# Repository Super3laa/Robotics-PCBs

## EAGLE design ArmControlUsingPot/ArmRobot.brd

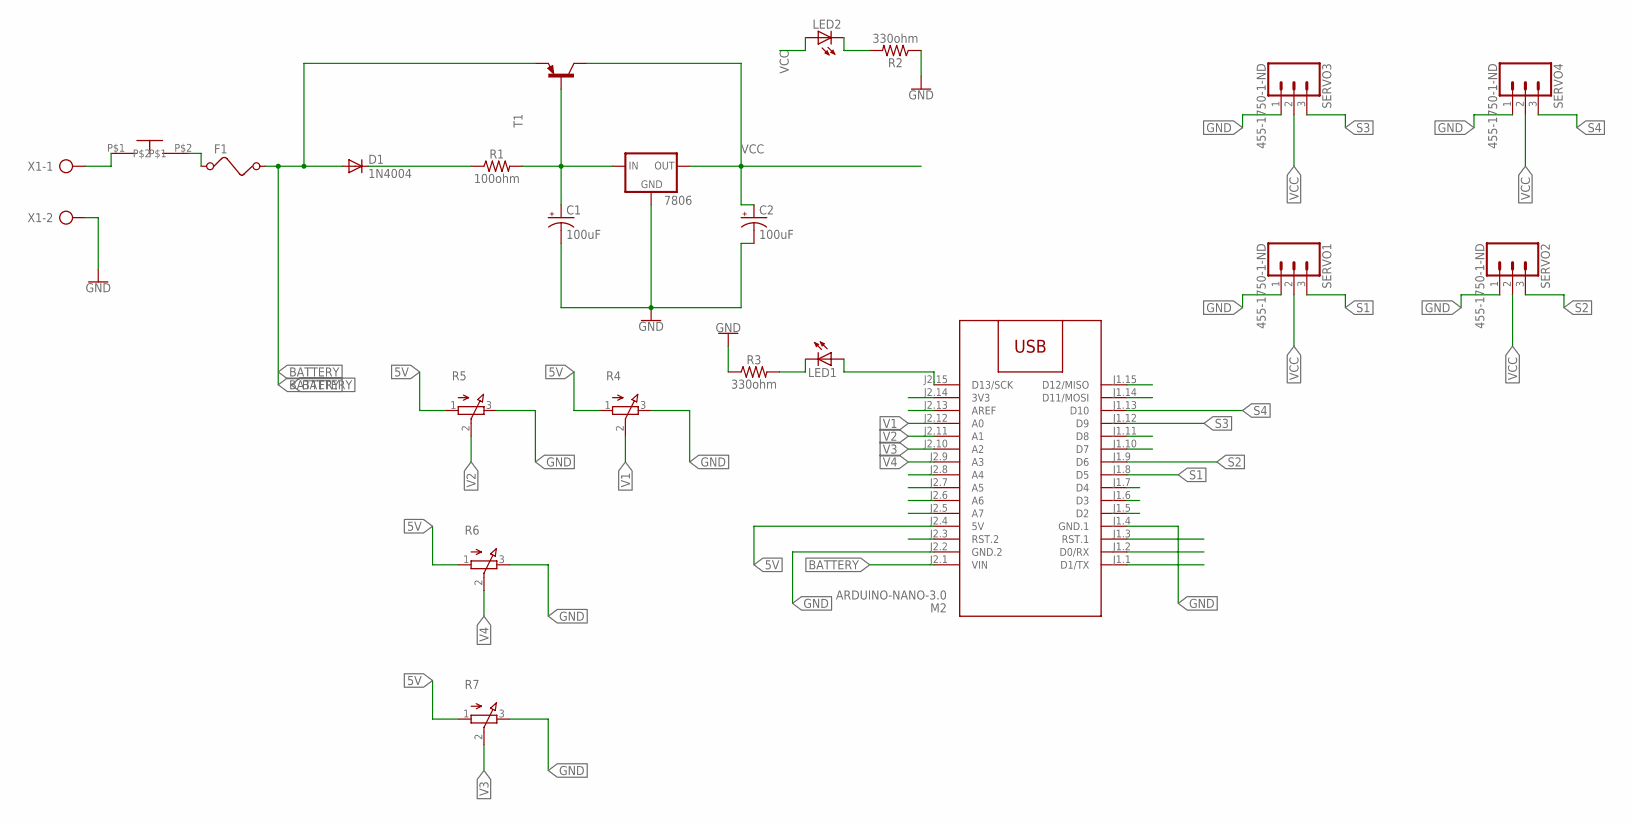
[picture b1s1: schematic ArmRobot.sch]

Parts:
7806: 78XXS
C1, C2: 100uF; CPOL-RADIAL-2.5MM-6.5MM
D1: 1N4004; DO41-10
F1: FUSE
LED1, LED2: LED3MM
M2: ARDUINO-NANO-3.0
R1: 100ohm; AXIAL-0.3
R2, R3: 330ohm; AXIAL-0.3
R4, R5, R6, R7: 3RP/1610N
SERVO1, SERVO2, SERVO3, SERVO4: 455-1750-1-ND; 1X03
T1: -PNP-TO220V; TO220V
U$1: ON_OFF
X1: AK500/2-H

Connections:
5V: M2.J2.4 (5V), R4.1 (A), R5.1 (A), R6.1 (A), R7.1 (A)
BATTERY: D1.A, F1.2, M2.J2.1 (VIN), T1.3 (E)
BATTERY_INPUT: U$1.P$1, X1.1
GND: 7806.GND, C1.2 (-), C2.2 (-), M2.J1.4 (GND.1), M2.J2.2 (GND.2), R2.P$1 (1), R3.P$1 (1), R4.3 (E), R5.3 (E), R6.3 (E), R7.3 (E), SERVO1.1, SERVO2.1, SERVO3.1, SERVO4.1, X1.2
unnamed: LED1.K (C), R3.P$2 (2)
unnamed: LED1.A, M2.J2.15 (D13/SCK)
unnamed: D1.C, R1.P$1 (1)
unnamed: 7806.IN, C1.1 (+), R1.P$2 (2), T1.1 (B)
unnamed: F1.1, U$1.P$2
unnamed: LED2.K (C), R2.P$2 (2)
S1: M2.J1.8 (D5), SERVO1.3
S2: M2.J1.9 (D6), SERVO2.3
S3: M2.J1.12 (D9), SERVO3.3
S4: M2.J1.13 (D10), SERVO4.3
V1: M2.J2.12 (A0), R4.2 (S)
V2: M2.J2.11 (A1), R5.2 (S)
V3: M2.J2.10 (A2), R7.2 (S)
V4: M2.J2.9 (A3), R6.2 (S)
VCC: 7806.OUT, C2.1 (+), LED2.A, SERVO1.2, SERVO2.2, SERVO3.2, SERVO4.2, T1.2 (C)

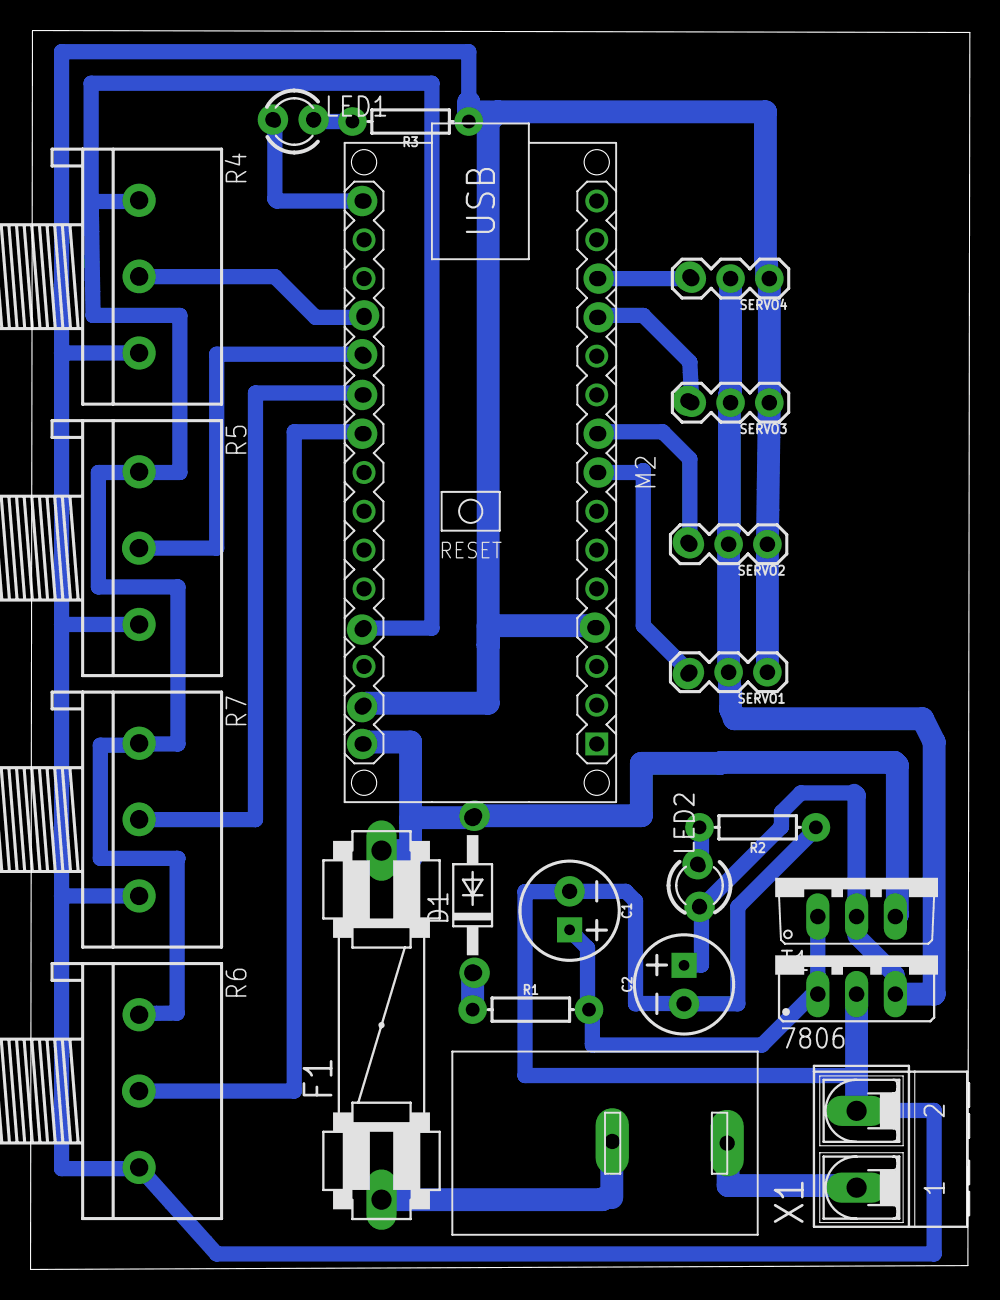
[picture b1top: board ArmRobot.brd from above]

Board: 2 copper layers, 61.5 x 81.1 mm, 22 parts (0 on the bottom side), 19 nets.

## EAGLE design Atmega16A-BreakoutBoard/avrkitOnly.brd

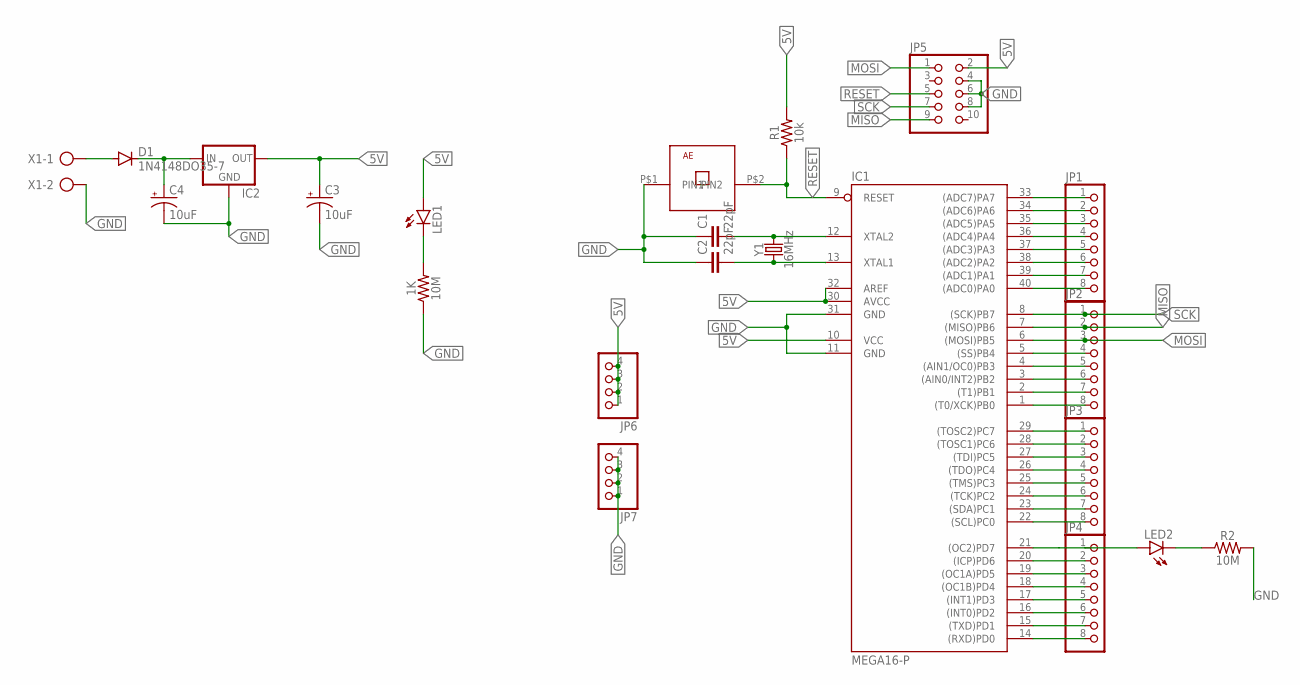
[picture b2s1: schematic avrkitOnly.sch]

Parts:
1K: 10M; AXIAL-0.3
C1, C2: 22pF; CAP-PTH-2.54
C3, C4: 10uF; CPOL-RADIAL-2.5MM-5MM
D1: 1N4148DO35-7; DO35-7
IC1: MEGA16-P; DIL40
IC2: 78XXS
JP1, JP2, JP3, JP4: PINHD-1X8; 1X08
JP5: PINHD-2X5; 2X05
JP6, JP7: PINHD-1X4; 1X04
LED1, LED2: LED3MM
R1: 10k; AXIAL-0.3
R2: 10M; AXIAL-0.3
U$1: PUSHBUTTON-AE
X1: AK500/2-H
Y1: 16MHz; HC49US

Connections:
5V: C3.1 (+), IC1.10 (VCC), IC1.30 (AVCC), IC1.32 (AREF), IC2.OUT, JP5.2, JP6.1, JP6.2, JP6.3, JP6.4, LED1.A, R1.P$2 (2)
GND: 1K.P$1 (1), C1.1, C2.1, C3.2 (-), C4.2 (-), IC1.11 (GND), IC1.31 (GND), IC2.GND, JP5.4, JP5.6, JP5.8, JP7.1, JP7.2, JP7.3, JP7.4, R2.P$2 (2), U$1.P$1 (PIN1), X1.2
MISO: IC1.7 ((MISO)PB6), JP2.2, JP5.9
MOSI: IC1.6 ((MOSI)PB5), JP2.3, JP5.1
unnamed: C1.2, IC1.12 (XTAL2), Y1.2
unnamed: C2.2, IC1.13 (XTAL1), Y1.1
unnamed: C4.1 (+), D1.C, IC2.IN
unnamed: 1K.P$2 (2), LED1.K (C)
unnamed: LED2.K (C), R2.P$1 (1)
unnamed: D1.A, X1.1
unnamed: IC1.33 ((ADC7)PA7), JP1.1
unnamed: IC1.34 ((ADC6)PA6), JP1.2
unnamed: IC1.35 ((ADC5)PA5), JP1.3
unnamed: IC1.36 ((ADC4)PA4), JP1.4
unnamed: IC1.37 ((ADC3)PA3), JP1.5
unnamed: IC1.38 ((ADC2)PA2), JP1.6
unnamed: IC1.39 ((ADC1)PA1), JP1.7
unnamed: IC1.40 ((ADC0)PA0), JP1.8
unnamed: IC1.5 ((SS)PB4), JP2.4
unnamed: IC1.4 ((AIN1/OC0)PB3), JP2.5
unnamed: IC1.3 ((AIN0/INT2)PB2), JP2.6
unnamed: IC1.2 ((T1)PB1), JP2.7
unnamed: IC1.1 ((T0/XCK)PB0), JP2.8
unnamed: IC1.29 ((TOSC2)PC7), JP3.1
unnamed: IC1.28 ((TOSC1)PC6), JP3.2
unnamed: IC1.27 ((TDI)PC5), JP3.3
unnamed: IC1.26 ((TDO)PC4), JP3.4
unnamed: IC1.25 ((TMS)PC3), JP3.5
unnamed: IC1.24 ((TCK)PC2), JP3.6
unnamed: IC1.23 ((SDA)PC1), JP3.7
unnamed: IC1.22 ((SCL)PC0), JP3.8
unnamed: IC1.21 ((OC2)PD7), JP4.1, LED2.A
unnamed: IC1.20 ((ICP)PD6), JP4.2
unnamed: IC1.19 ((OC1A)PD5), JP4.3
unnamed: IC1.18 ((OC1B)PD4), JP4.4
unnamed: IC1.17 ((INT1)PD3), JP4.5
unnamed: IC1.16 ((INT0)PD2), JP4.6
unnamed: IC1.15 ((TXD)PD1), JP4.7
unnamed: IC1.14 ((RXD)PD0), JP4.8
RESET: IC1.9 (RESET), JP5.5, R1.P$1 (1), U$1.P$2 (PIN2)
SCK: IC1.8 ((SCK)PB7), JP2.1, JP5.7

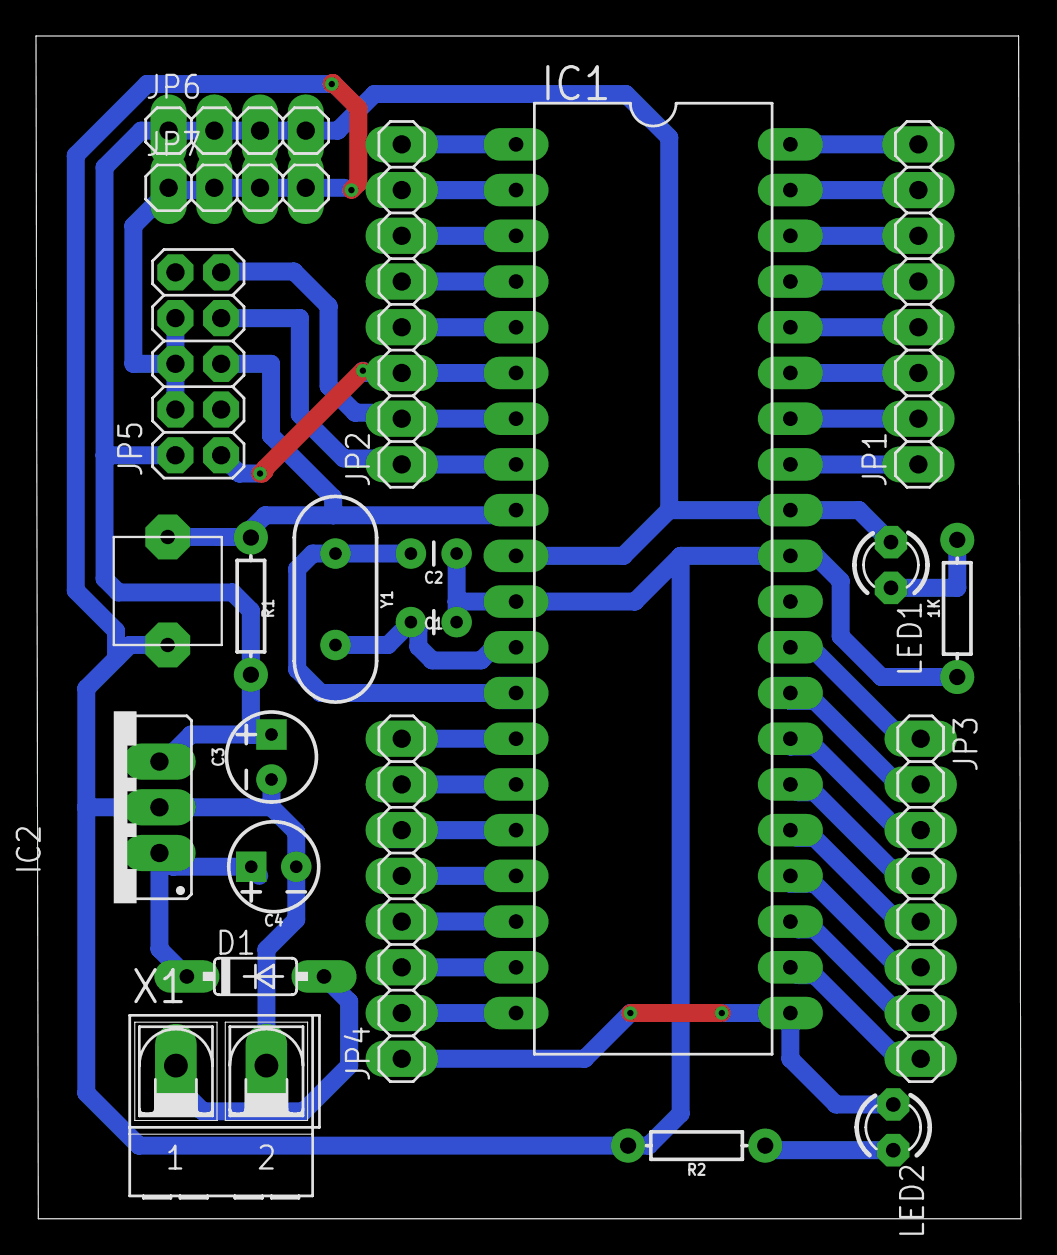
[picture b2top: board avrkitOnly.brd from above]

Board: 2 copper layers, 54.7 x 65.7 mm, 22 parts (0 on the bottom side), 41 nets.

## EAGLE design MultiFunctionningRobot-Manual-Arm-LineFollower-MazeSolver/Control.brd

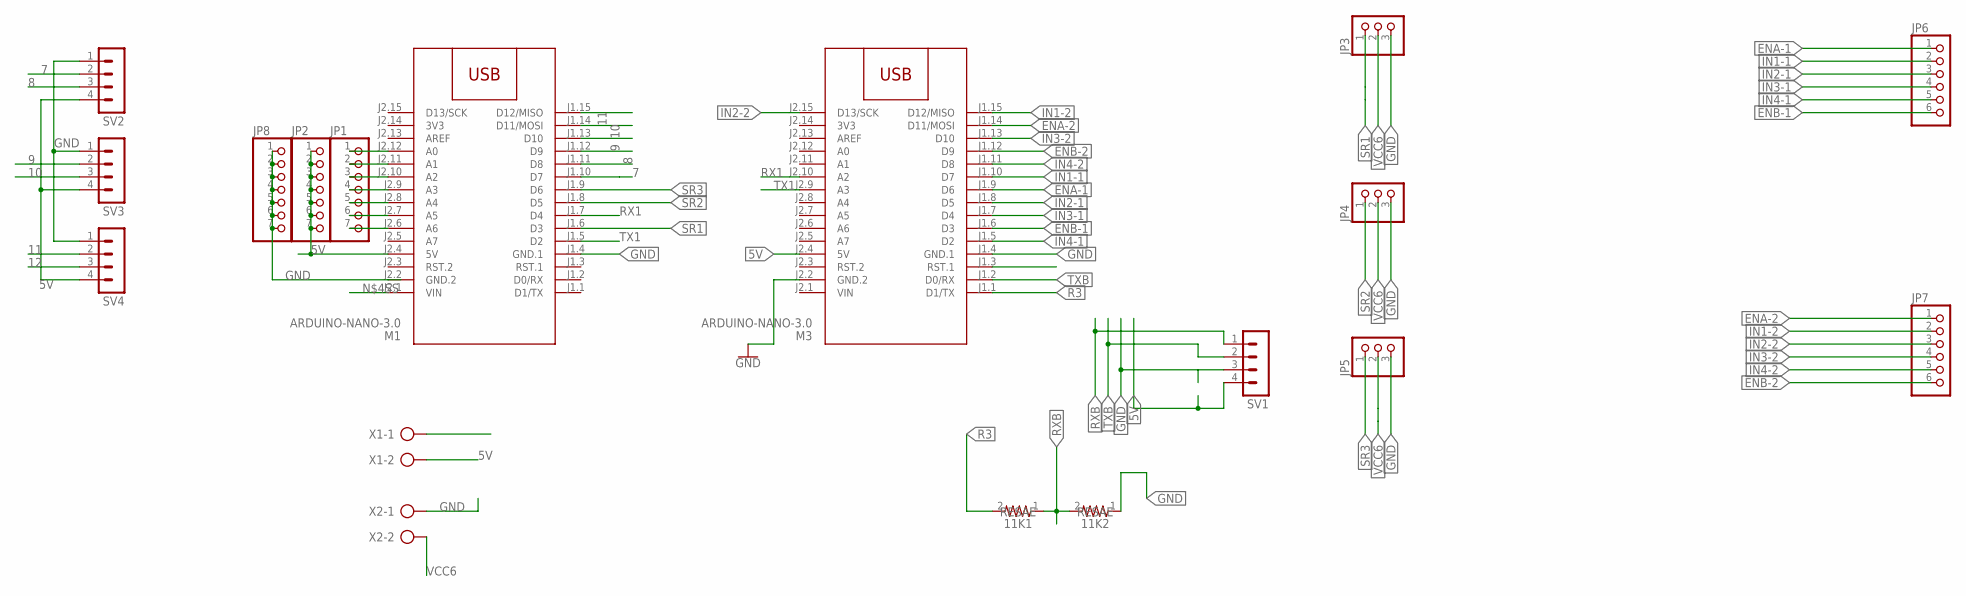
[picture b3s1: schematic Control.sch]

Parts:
11K1, 11K2: RESAE; RESAD846W63L520D250B
JP1, JP2, JP8: PINHD-1X7; 1X07
JP3, JP4, JP5: PINHD-1X3; 1X03
JP6, JP7: PINHD-1X6; 1X06
M1, M3: ARDUINO-NANO-3.0
SV1, SV2, SV3, SV4: MA04-1
X1, X2: AK500/2-H

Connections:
3V3: M1.J2.14 (3V3), M3.J2.14 (3V3)
5V: JP2.1, JP2.2, JP2.3, JP2.4, JP2.5, JP2.6, JP2.7, M1.J2.4 (5V), M3.J2.4 (5V), SV1.4, SV2.4, SV3.4, SV4.4, X1.2
7: M1.J1.10 (D7), SV2.2
8: M1.J1.11 (D8), SV2.3
9: M1.J1.12 (D9), SV3.2
10: M1.J1.13 (D10), SV3.3
11: M1.J1.14 (D11/MOSI), SV4.2
12: M1.J1.15 (D12/MISO), SV4.3
ENA-1: JP6.1, M3.J1.9 (D6)
ENA-2: JP7.1, M3.J1.14 (D11/MOSI)
ENB-1: JP6.6, M3.J1.6 (D3)
ENB-2: JP7.6, M3.J1.12 (D9)
GND: 11K2.1, JP3.3, JP4.3, JP5.3, JP8.1, JP8.2, JP8.3, JP8.4, JP8.5, JP8.6, JP8.7, M1.J1.4 (GND.1), M1.J2.2 (GND.2), M3.J1.4 (GND.1), M3.J2.2 (GND.2), SV1.3, SV2.1, SV3.1, SV4.1, X1.1, X2.1
IN1-1: JP6.2, M3.J1.10 (D7)
IN1-2: JP7.2, M3.J1.15 (D12/MISO)
IN2-1: JP6.3, M3.J1.8 (D5)
IN2-2: JP7.3, M3.J2.15 (D13/SCK)
IN3-1: JP6.4, M3.J1.7 (D4)
IN3-2: JP7.4, M3.J1.13 (D10)
IN4-1: JP6.5, M3.J1.5 (D2)
IN4-2: JP7.5, M3.J1.11 (D8)
unnamed: JP1.1, M1.J2.12 (A0)
unnamed: JP1.2, M1.J2.11 (A1)
unnamed: JP1.3, M1.J2.10 (A2)
unnamed: JP1.4, M1.J2.9 (A3)
unnamed: JP1.5, M1.J2.8 (A4)
unnamed: JP1.6, M1.J2.7 (A5)
unnamed: JP1.7, M1.J2.6 (A6)
R3: 11K1.2, M3.J1.1 (D1/TX)
RX1: M1.J1.7 (D4), M3.J2.10 (A2)
RXB: 11K1.1, 11K2.2, SV1.1
SR1: JP3.1, M1.J1.6 (D3)
SR2: JP4.1, M1.J1.8 (D5)
SR3: JP5.1, M1.J1.9 (D6)
TX1: M1.J1.5 (D2), M3.J2.9 (A3)
TXB: M3.J1.2 (D0/RX), SV1.2
VCC6: JP3.2, JP4.2, JP5.2, X2.2
VIN: M3.J2.1 (VIN)

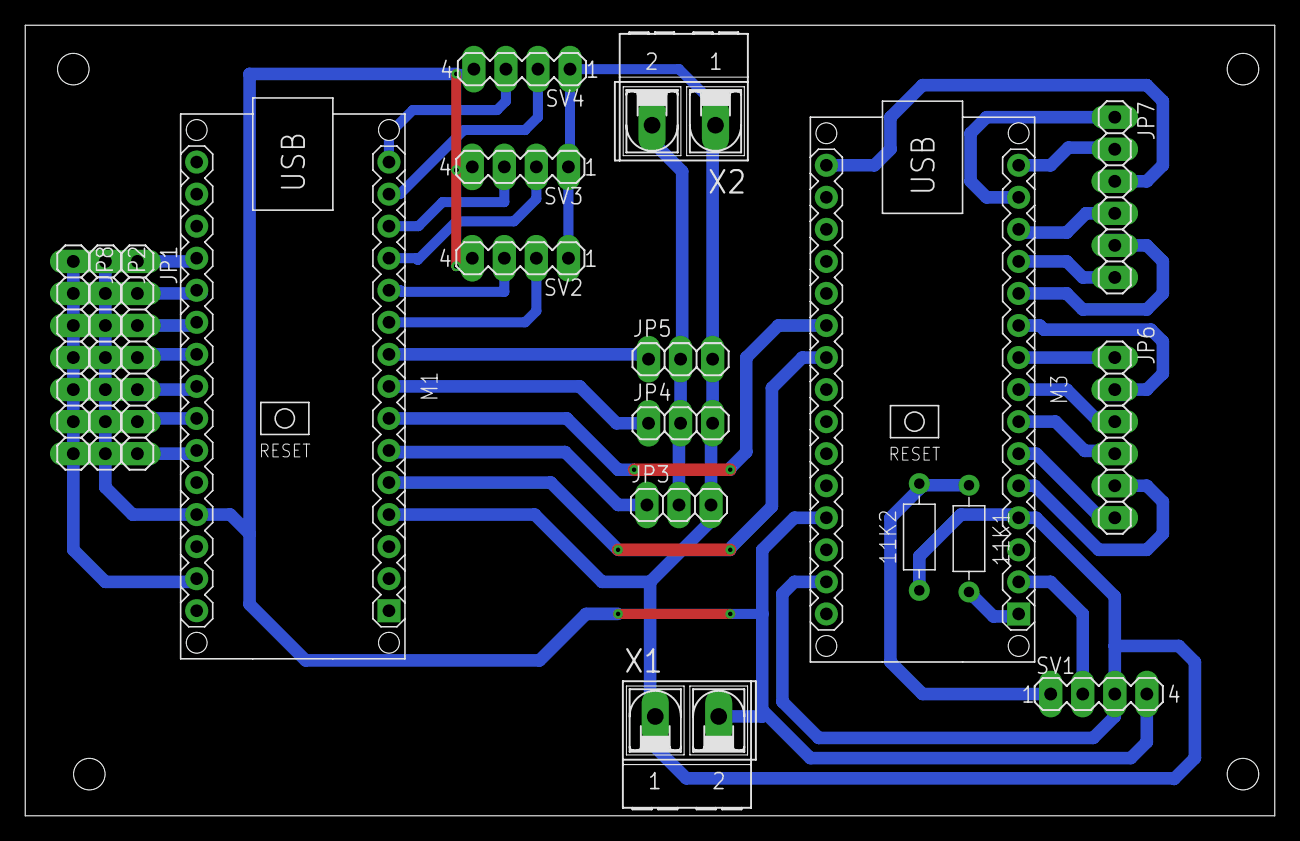
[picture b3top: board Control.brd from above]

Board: 2 copper layers, 99.0 x 62.7 mm, 18 parts (0 on the bottom side), 37 nets.

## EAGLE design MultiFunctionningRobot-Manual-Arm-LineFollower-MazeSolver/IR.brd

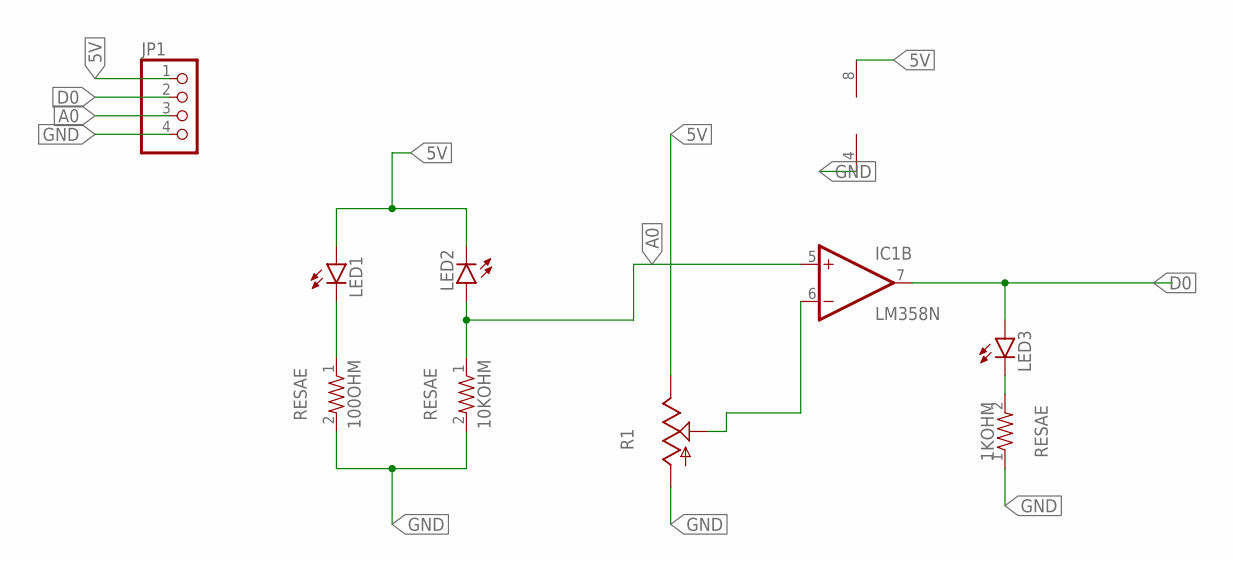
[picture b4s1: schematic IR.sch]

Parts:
1KOHM, 10KOHM, 100OHM: RESAE; RESAD846W63L520D250B
IC1: LM358N; DIL08
JP1: PINHD-1X4/90; 1X04/90
LED1, LED2: LED5MM
LED3: LED3MM
R1: TRIM_US-CA6V; CA6V

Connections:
5V: IC1.8 (V+), JP1.1, LED1.A, LED2.K (C), R1.E
A0: 10KOHM.1, IC1.5 (+IN), JP1.3, LED2.A
D0: IC1.7 (OUT), JP1.2, LED3.A
GND: 1KOHM.1, 10KOHM.2, 100OHM.2, IC1.4 (V-), JP1.4, R1.A
unnamed: 100OHM.1, LED1.K (C)
unnamed: IC1.6 (-IN), R1.S
unnamed: 1KOHM.2, LED3.K (C)

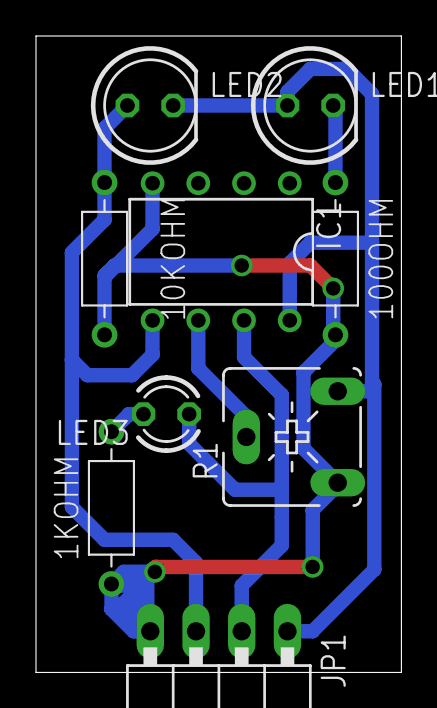
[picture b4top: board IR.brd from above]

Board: 2 copper layers, 20.3 x 35.4 mm, 9 parts (0 on the bottom side), 7 nets.

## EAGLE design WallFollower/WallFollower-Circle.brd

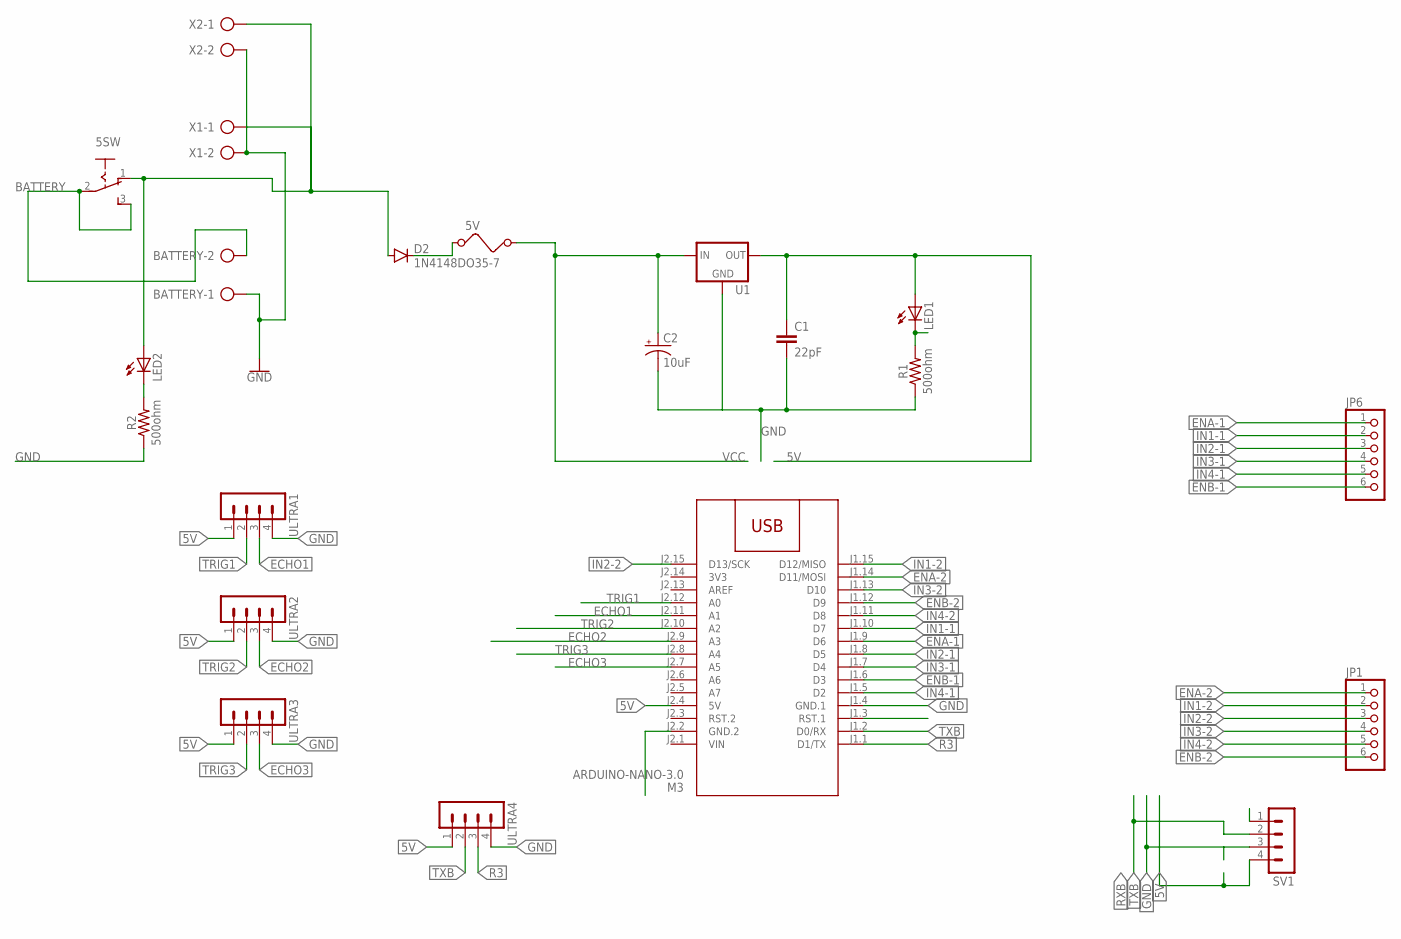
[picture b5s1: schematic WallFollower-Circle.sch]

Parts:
5SW: 255SB
5V: FUSE
BATTERY: AK500/2-H
C1: 22pF; CAP-PTH-2.54
C2: 10uF; CPOL-RADIAL-2.5MM-5MM
D2: 1N4148DO35-7; DO35-7
JP1, JP6: PINHD-1X6; 1X06
LED1, LED2: LED3MM
M3: ARDUINO-NANO-3.0
R1, R2: 500ohm; AXIAL-0.3
SV1: MA04-1
U1: 78XXS
ULTRA1, ULTRA2, ULTRA3, ULTRA4: MA04-1
X1, X2: AK500/2-H

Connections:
3V3: M3.J2.14 (3V3)
5V: C1.1, LED1.A, M3.J2.4 (5V), SV1.4, U1.OUT, ULTRA1.1, ULTRA2.1, ULTRA3.1, ULTRA4.1
5V1: 5SW.1 (O), D2.A, LED2.A, X1.1, X2.1
BATTERY: 5SW.2, 5SW.3 (S), BATTERY.2
ECHO1: M3.J2.11 (A1), ULTRA1.3
ECHO2: M3.J2.9 (A3), ULTRA2.3
ECHO3: M3.J2.7 (A5), ULTRA3.3
ENA-1: JP6.1, M3.J1.9 (D6)
ENA-2: JP1.1, M3.J1.14 (D11/MOSI)
ENB-1: JP6.6, M3.J1.6 (D3)
ENB-2: JP1.6, M3.J1.12 (D9)
GND: BATTERY.1, C1.2, C2.2 (-), M3.J1.4 (GND.1), M3.J2.2 (GND.2), R1.P$1 (1), R2.P$1 (1), SV1.3, U1.GND, ULTRA1.4, ULTRA2.4, ULTRA3.4, ULTRA4.4, X1.2, X2.2
IN1-1: JP6.2, M3.J1.10 (D7)
IN1-2: JP1.2, M3.J1.15 (D12/MISO)
IN2-1: JP6.3, M3.J1.8 (D5)
IN2-2: JP1.3, M3.J2.15 (D13/SCK)
IN3-1: JP6.4, M3.J1.7 (D4)
IN3-2: JP1.4, M3.J1.13 (D10)
IN4-1: JP6.5, M3.J1.5 (D2)
IN4-2: JP1.5, M3.J1.11 (D8)
unnamed: 5V.1, D2.C
unnamed: LED2.K (C), R2.P$2 (2)
unnamed: LED1.K (C), R1.P$2 (2)
R3: M3.J1.1 (D1/TX), ULTRA4.3
RXB: SV1.1
TRIG1: M3.J2.12 (A0), ULTRA1.2
TRIG2: M3.J2.10 (A2), ULTRA2.2
TRIG3: M3.J2.8 (A4), ULTRA3.2
TXB: M3.J1.2 (D0/RX), SV1.2, ULTRA4.2
VCC: 5V.2, C2.1 (+), U1.IN
VIN: M3.J2.1 (VIN)

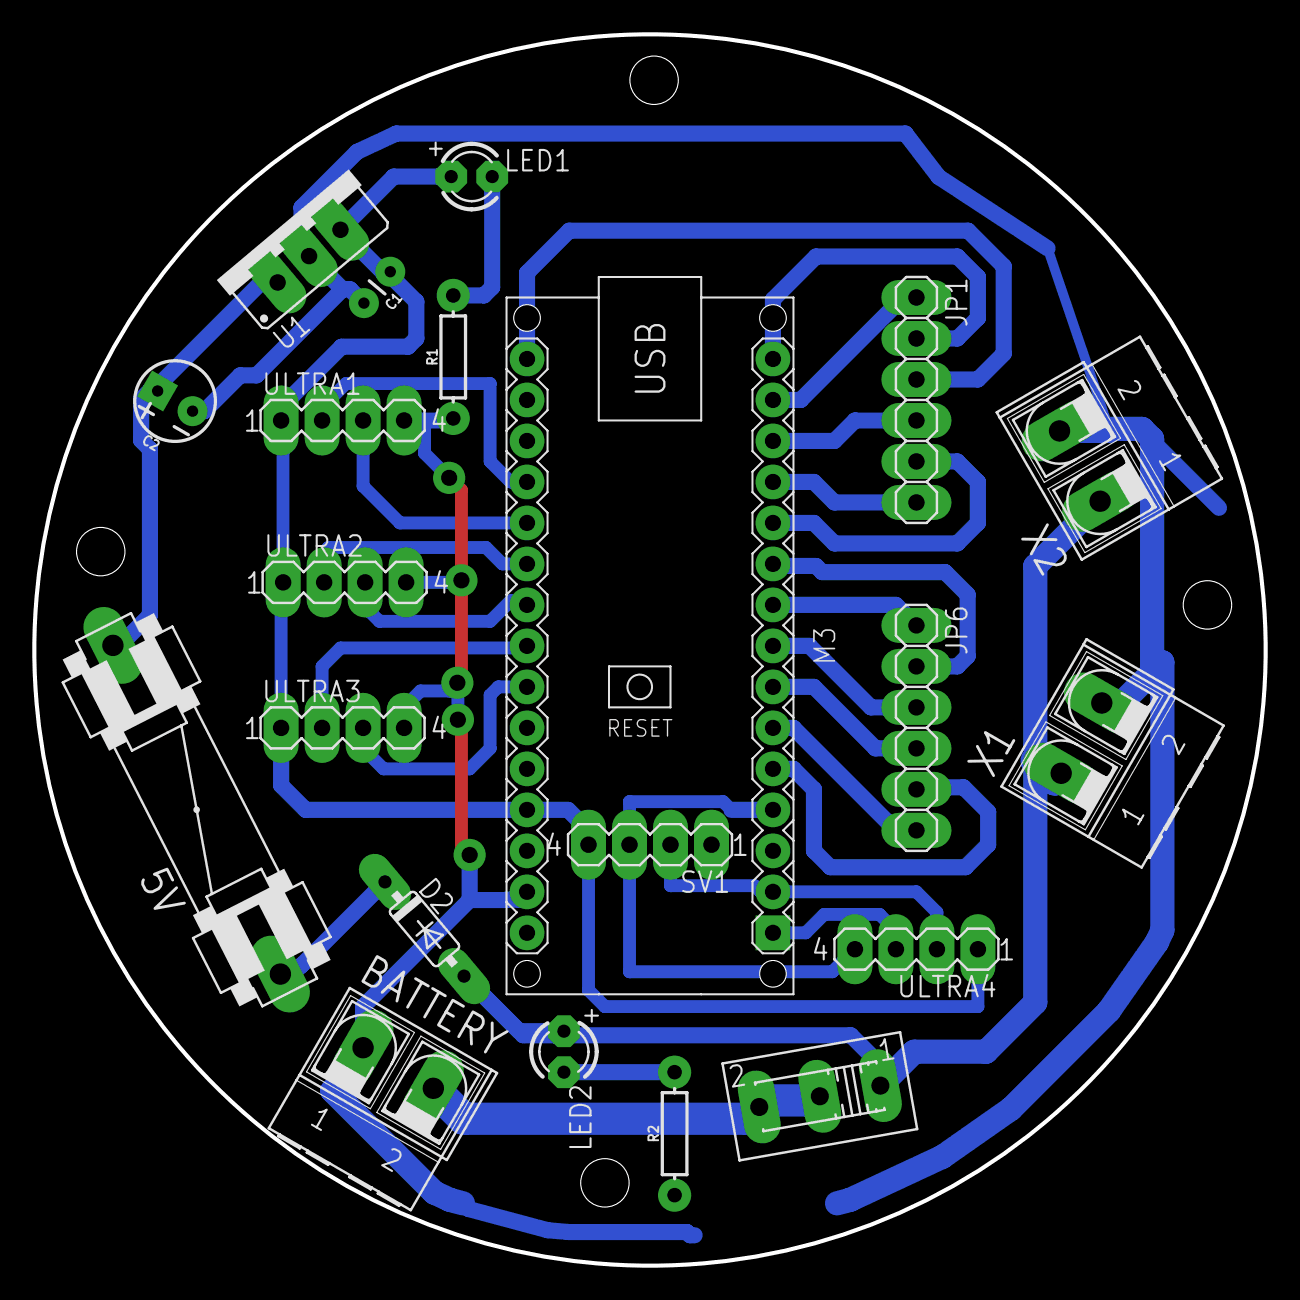
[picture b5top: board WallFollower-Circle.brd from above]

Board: 2 copper layers, 76.3 x 76.3 mm, 21 parts (0 on the bottom side), 28 nets.

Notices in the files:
parts and their libraries:
SparkFun-Capacitors: Licensing: Creative Commons ShareAlike 4.0 International - https://creativecommons.org/licenses/by-sa/4.0
diy-modules: Released under the Creative Commons Attribution 4.0 International License: http://creativecommons.org/licenses/by/4.0
